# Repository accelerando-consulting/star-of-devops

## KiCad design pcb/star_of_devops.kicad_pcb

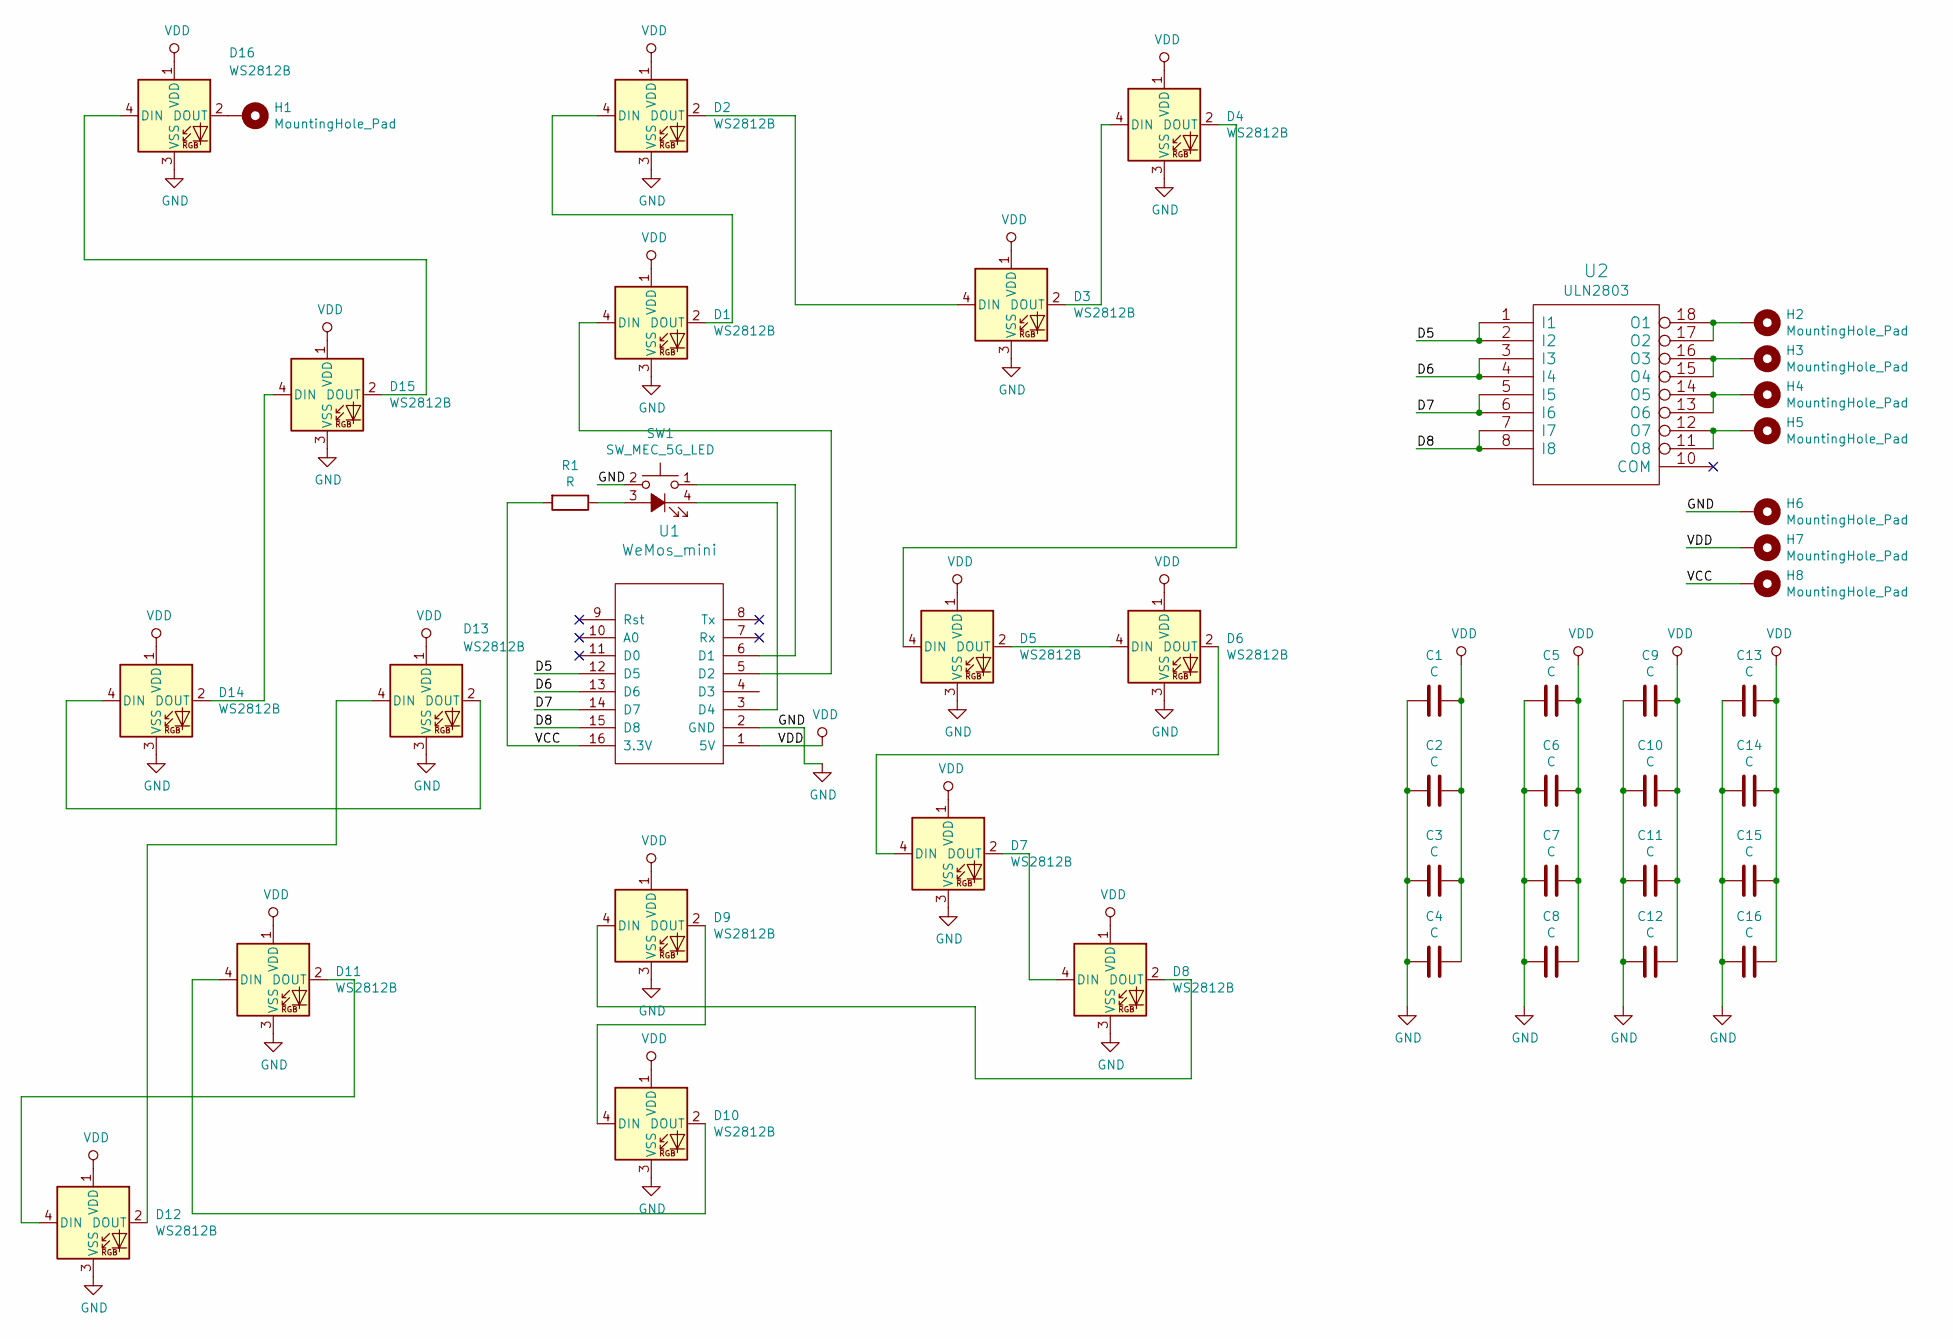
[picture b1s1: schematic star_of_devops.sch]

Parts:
C1, C2, C3, C4, C5, C6, C7, C8, C9, C10, C11, C12, C13, C14, C15, C16: C; C_0805_HandSoldering
D1, D2, D3, D4, D5, D6, D7, D8, D9, D10, D11, D12, D13, D14, D15, D16: WS2812B; LED_WS2812B-PLCC4
H1, H2, H3, H4, H5, H6, H7, H8: MountingHole_Pad; pin_sewable_2.5mm
R1: R; R_0805_HandSoldering
SW1: SW_MEC_5G_LED; SW_PUSH-12mm-LED
U1: WeMos_mini; wemos-d1-mini-connectors-only
U2: ULN2803; SOIC-18W_7.5x11.6mm_Pitch1.27mm

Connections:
/D5: U1.12 (D5), U2.1 (I1), U2.2 (I2)
/D6: U1.13 (D6), U2.3 (I3), U2.4 (I4)
/D7: U1.14 (D7), U2.5 (I5), U2.6 (I6)
/D8: U1.15 (D8), U2.7 (I7), U2.8 (I8)
/VCC: H8.1, R1.2, U1.16 (3.3V)
GND: C1.2, C2.2, C3.2, C4.2, C5.2, C6.2, C7.2, C8.2, C9.2, C10.2, C11.2, C12.2, C13.2, C14.2, C15.2, C16.2, D1.3 (VSS), D2.3 (VSS), D3.3 (VSS), D4.3 (VSS), D5.3 (VSS), D6.3 (VSS), D7.3 (VSS), D8.3 (VSS), D9.3 (VSS), D10.3 (VSS), D11.3 (VSS), D12.3 (VSS), D13.3 (VSS), D14.3 (VSS), D15.3 (VSS), D16.3 (VSS), H6.1, SW1.2, U1.2 (GND), U2.9 (GND)
unnamed: D1.2 (DOUT), D2.4 (DIN)
unnamed: D1.4 (DIN), U1.5 (D2)
unnamed: D2.2 (DOUT), D3.4 (DIN)
unnamed: D3.2 (DOUT), D4.4 (DIN)
unnamed: D4.2 (DOUT), D5.4 (DIN)
unnamed: D5.2 (DOUT), D6.4 (DIN)
unnamed: D6.2 (DOUT), D7.4 (DIN)
unnamed: D7.2 (DOUT), D8.4 (DIN)
unnamed: D8.2 (DOUT), D9.4 (DIN)
unnamed: D10.2 (DOUT), D11.4 (DIN)
unnamed: D9.2 (DOUT), D10.4 (DIN)
unnamed: D11.2 (DOUT), D12.4 (DIN)
unnamed: D12.2 (DOUT), D13.4 (DIN)
unnamed: D13.2 (DOUT), D14.4 (DIN)
unnamed: D14.2 (DOUT), D15.4 (DIN)
unnamed: D15.2 (DOUT), D16.4 (DIN)
unnamed: D16.2 (DOUT), H1.1
unnamed: H2.1, U2.17 (O2), U2.18 (O1)
unnamed: H3.1, U2.15 (O4), U2.16 (O3)
unnamed: H4.1, U2.13 (O6), U2.14 (O5)
unnamed: H5.1, U2.11 (O8), U2.12 (O7)
unnamed: R1.1, SW1.3 (A)
unnamed: SW1.1, U1.6 (D1)
unnamed: SW1.4 (K), U1.3 (D4)
VDD: C1.1, C2.1, C3.1, C4.1, C5.1, C6.1, C7.1, C8.1, C9.1, C10.1, C11.1, C12.1, C13.1, C14.1, C15.1, C16.1, D1.1 (VDD), D2.1 (VDD), D3.1 (VDD), D4.1 (VDD), D5.1 (VDD), D6.1 (VDD), D7.1 (VDD), D8.1 (VDD), D9.1 (VDD), D10.1 (VDD), D11.1 (VDD), D12.1 (VDD), D13.1 (VDD), D14.1 (VDD), D15.1 (VDD), D16.1 (VDD), H7.1, U1.1 (5V)

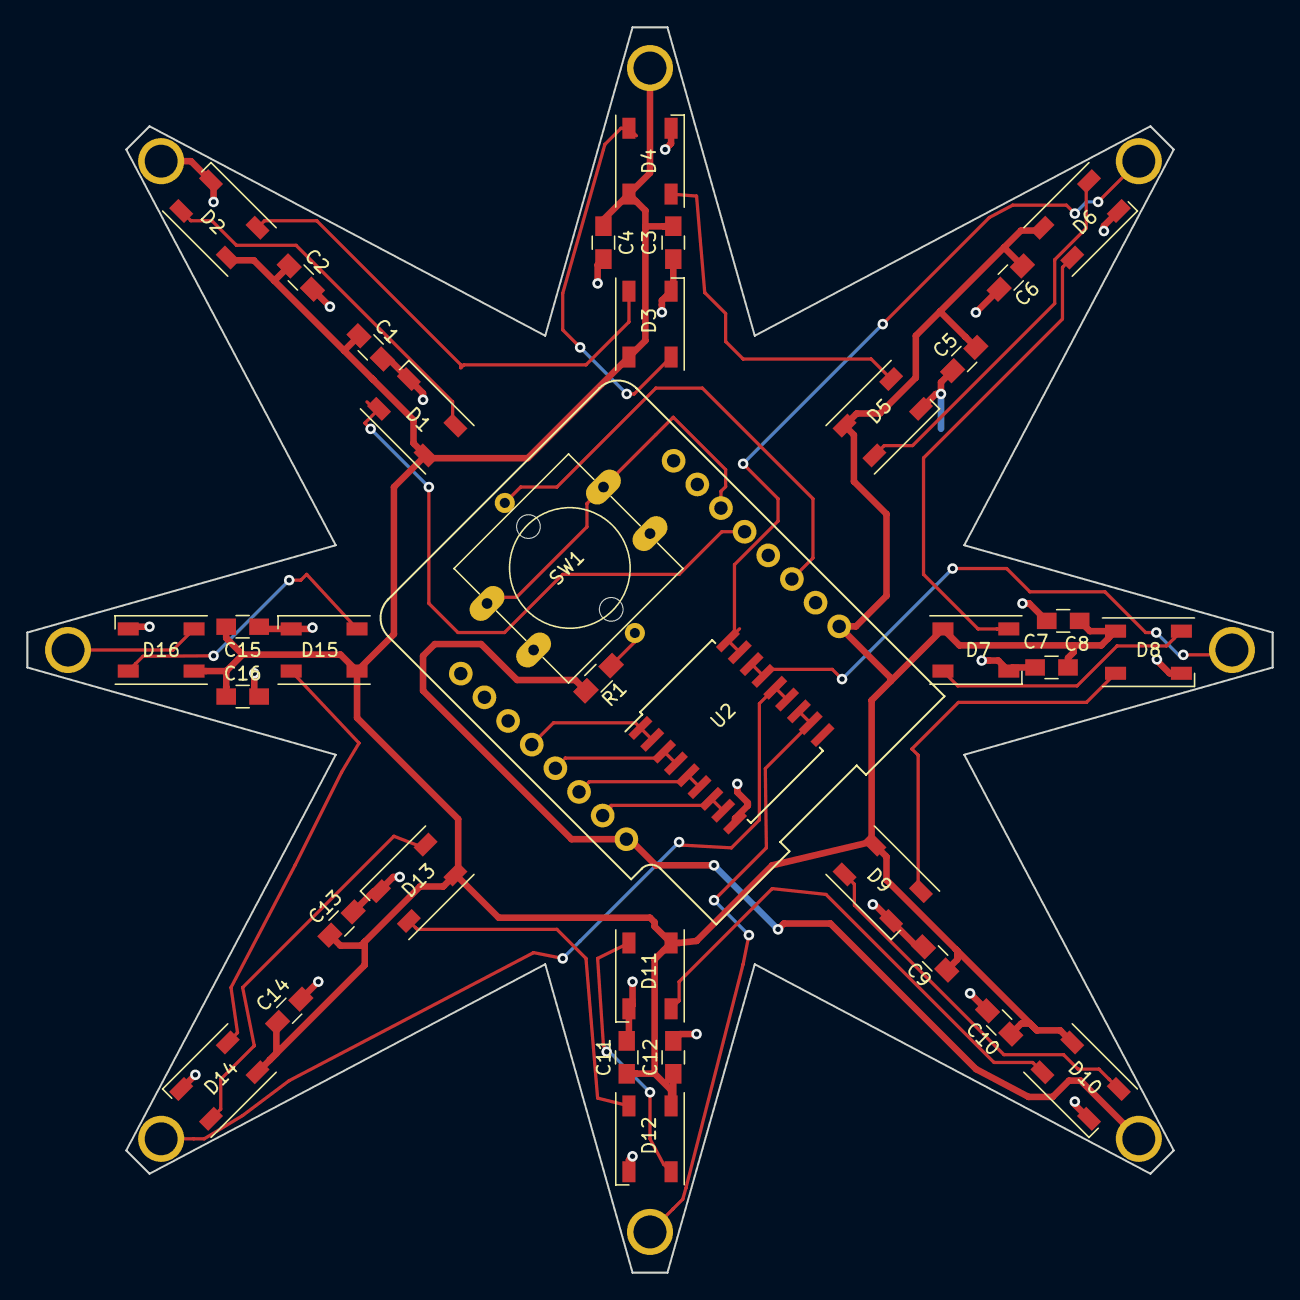
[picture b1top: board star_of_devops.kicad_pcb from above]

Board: 2 copper layers, 94.6 x 94.6 mm, 44 parts (0 on the bottom side), 31 nets.

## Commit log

2018-11-19 An LED christmas star shield for Lolin D1 Mini
2019-01-23 Import the demo code for standalone star
